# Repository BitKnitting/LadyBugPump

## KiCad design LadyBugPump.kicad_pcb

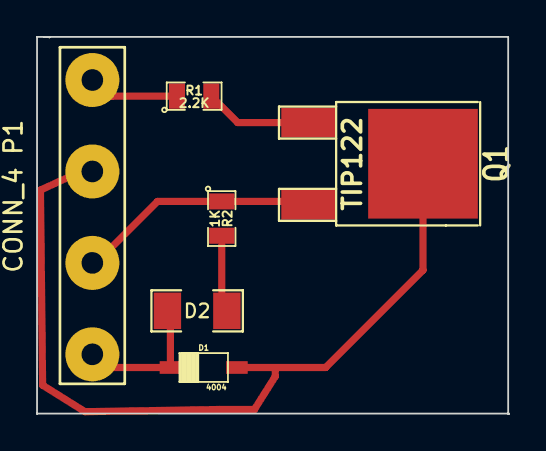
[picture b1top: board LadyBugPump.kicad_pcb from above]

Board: 2 copper layers, 26.2 x 21.0 mm, 6 parts (0 on the bottom side), 6 nets.

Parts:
D1: 4004; SOD-123
D2: LED; SM1206
P1: CONN_4; LB_CONN_WIDE_4
Q1: TIP122; DPAK2
R1: 2.2K; SM0805
R2: 1K; SM0805

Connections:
+12V: D1.2, D2.1, P1.4
/ARD: P1.1, R1.1
/Switch: D1.1, P1.2, Q1.2
GND: P1.3, Q1.3, R2.1
unnamed: D2.2, R2.2
unnamed: Q1.1, R1.2
